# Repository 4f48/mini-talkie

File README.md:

# mini-talkie

A little 868 MHz walkie-talkie with LoRa radio for long ranges with built-in battery and USB-C charging.

### Features:
- 100% off-grid. Works anywhere!
- Long range: multiple kilometers in ideal conditions
- Long battery life: 1200 mAh lithium-polymer battery
- Convenient USB-C charging
- Swappable antenna: use any 868 MHz antenna you want
- Multiple modes: push-to-talk, voice activation
- Small size: fits in your pockets

### Usage:
1. Turn it on using the switch on the left.
2. Start talking! Use the push-to-talk button, or switch to voice activation and talk hands free.
3. Battery low? Plug it in to your regular phone charger.

## Why?
All the walkie-talkies I tried before have too short range, have too many fancy features I would never use, or are very expensive. This walkie-talkie is unique in the way that it uses LoRa radio, making it operate through exceptional ranges. It's also dead simple: no screen, no dials. It doesn't have many extra features, but the ones it has just work. It is also not very expensive to build. It's great for hiking so nobody gets lost, or multiple-car road trips to keep in contact with the other cars without phone calls.

## Assembly
You can actually build a mini-talkie for yourself. All you need is the PCB, SMD components, a speaker, an antenna and internal antenna cable. Below is a rough guide to making one.

### 1. PCB and components

The printed circuit board has to be manufactured somewhere. I recommend [Aisler](https://aisler.net) or [JLCPCB](https://jlcpcb.com), but any similar services work. You can find the source files for the PCB in [/pcb](./pcb). Make sure to order the PCBA (assembly) service if you are not comfortable soldering smaller sized components.

You also need some other components ordered. Check out the [Bill of Materials](./bom.csv) which includes links to help you order them easily.

| Component                          | MPN                | Reference                     | Qty | Link                                                                            |
|------------------------------------|--------------------|-------------------------------|-----|---------------------------------------------------------------------------------|
| 0603 2.2 µF capacitor              | CC0603KRX7R5BB225  | C1,C2                         | 2   | https://www.digikey.hu/short/4rjpq33n                                           |
| 0603 100 nF capacitor              | CC0603KRX7R5BB104  | C3,C4,C5,C6,C7,C9,C14,C18,C19 | 9   | https://www.digikey.hu/short/dt7hb4qj                                           |
| 0805 10 µF capacitor               | CL21A106KQFNNNG    | C8,C10,C11,C12,C13,C20        | 6   | https://www.digikey.hu/short/tvz058r0                                           |
| 0603 1 µF capacitor                | CL10A105KQ8NNNC    | C15,C16                       | 2   | https://www.digikey.hu/short/z9n48j83                                           |
| 0603 10 µF capacitor               | GRM188R60J106KE47D | C17                           | 1   | https://www.digikey.hu/short/4j9w29qw                                           |
| Schottky diode                     | B0520WS-7-F        | D1                            | 1   | https://www.digikey.hu/short/ht5bt73v                                           |
| 0805 orange LED                    | LTST-C170KFKT      | D2                            | 1   | https://www.digikey.hu/short/45p872b7                                           |
| 0603 ferrite bead 600 Ω @100 MHz   | BLM18KG601SN1D     | FB1                           | 1   | https://www.digikey.hu/short/0mqd98np                                           |
| SWD connector                      | BM03B-SRSS-TB      | J1                            | 1   | https://www.digikey.hu/short/5p581w55                                           |
| USB-C receptacle                   | USB4085-GF-A       | J2                            | 1   | https://www.digikey.hu/short/b77q7dpn                                           |
| battery connector                  | S2B-PH-K-S         | J3                            | 1   | https://www.digikey.hu/short/4j185jz8                                           |
| speaker connector                  | S2B-PH-K-S         | J4                            | 1   | https://www.digikey.hu/short/4j185jz8                                           |
| microphone                         | TOW-3050P-B-R      | MK1                           | 1   | https://www.digikey.hu/short/pvdf25rr                                           |
| MOSFET                             | AO3401A            | Q1                            | 1   | https://www.digikey.hu/short/8rwf7289                                           |
| 0603 10 kΩ resistor                | RC0603FR-0710KL    | R1,R4,R5,R6                   | 4   | https://www.digikey.hu/short/b31dpcpj                                           |
| 0603 5.1 kΩ resistor               | RC0603FR-075K1L    | R2,R3,R7                      | 3   | https://www.digikey.hu/short/q0d4nh3t                                           |
| 0805 1 kΩ resistor                 | ESR10EZPF1001      | R8                            | 1   | https://www.digikey.hu/short/5hnt9d3r                                           |
| SP3T sliding right-angle switch    | OS103011MA7QP1C    | SW1                           | 1   | https://www.digikey.hu/short/jz8f2558                                           |
| SPDT sliding right-angle switch    | OS102011MA1QN1     | SW2                           | 1   | https://www.digikey.hu/short/1v0t4jtn                                           |
| SPST right-angle pushbutton switch | B3F-3152           | SW3                           | 1   | https://www.digikey.hu/short/0rj93f0h                                           |
| microcontroller                    | STM32H503CBT6      | U1                            | 1   | https://www.digikey.hu/short/n7f3hf4p                                           |
| LoRa chipset                       | 114993390          | U2                            | 1   | https://www.digikey.hu/short/prpdvndd                                           |
| amplifier                          | PAM8302AASCR       | U3                            | 1   | https://www.digikey.hu/short/0pzv4hpb                                           |
| battery charger                    | MCP73831T-2ACI/OT  | U4                            | 1   | https://www.digikey.hu/short/wfqbhvzq                                           |
| 3.3V LDO voltage regulator         | RT9080-33GJ5       | U5                            | 1   | https://www.digikey.hu/short/2h9019td                                           |
| speaker                            | 4227               | -                             | 1   | https://www.digikey.hu/short/59fcjjq4                                           |
| antenna                            | GHX-325ASA3B       | -                             | 1   | https://www.digikey.hu/short/fqjjtd0b                                           |
| antenna cable                      | 18568              | -                             | 1   | https://www.digikey.hu/short/jn7jd79m                                           |
| battery                            | AKY0622            | -                             | 1   | https://www.tme.eu/hu/details/aky-lp883440/akkumulatorok/akyga-battery/aky0622/ |
| 2-pin JST PH cable                 | 4714               | -                             | 1   | https://www.digikey.hu/short/8mm8t1d7                                           |

Total cost of components: $38,82/unit (excl. taxes)

### 2. Printed parts

mini-talkie's enclosure is made from 2 parts. These have to be made on a 3D printer. If you don't have access to a 3D priner, explore services like [JLC3DP](https://jlc3dp.com) that print and ship the parts to you.

You can find the source files in [/3d](./3d) and exported models [/3d/exports](./3d/exports) for printing in STEP format.

### 3. Soldering

A fine-tipped soldering iron and some flux is needed for this part. Refer to the PCB source files in [/pcb](./pcb) as a reference for placing the correct parts.

Skip this step if you ordered your PCBs assembled (PCBA).

In addition, you need to remove the included connectors from the speaker and battery and solder on the 2-pin JST PH connectors you ordered instead. You need to do this even if you ordered a PCBA.

### 4. Programming

You need a Raspberry Pi Zero (2) or a separate debugger. Connect it to the SWD port on the circuit board and load the firmware from [/firmware](./firmware).

> TODO: Complete this part with instructions once the code is actually done.

### 5. Assembly
1. Insert 3 threaded inserts in the correct holes on the bottom enclosure. Appropriate tools are needed for this step.
2. Install the antenna cable using the included washers and nut.
3. Peel the protective layer off the adhesive on the speaker and stick it on the top enclosure, behind the speaker grille, but in a way that it won't obstruct the microphone.
4. Drop the battery into the compartment under where the PCB goes and plug it into the board.
5. Place the board on the bottom enclosure so that the battery connector is facing down.
6. Plug in the speaker to the board, and put the top enclosure on the bottom, then screw all the M2.5 screws into the top enclosure. Those 3 screws hold everything together, so make sure they are secure.
7. Compete the build by installing your SMA antenna on the top.

## Fallout Zine

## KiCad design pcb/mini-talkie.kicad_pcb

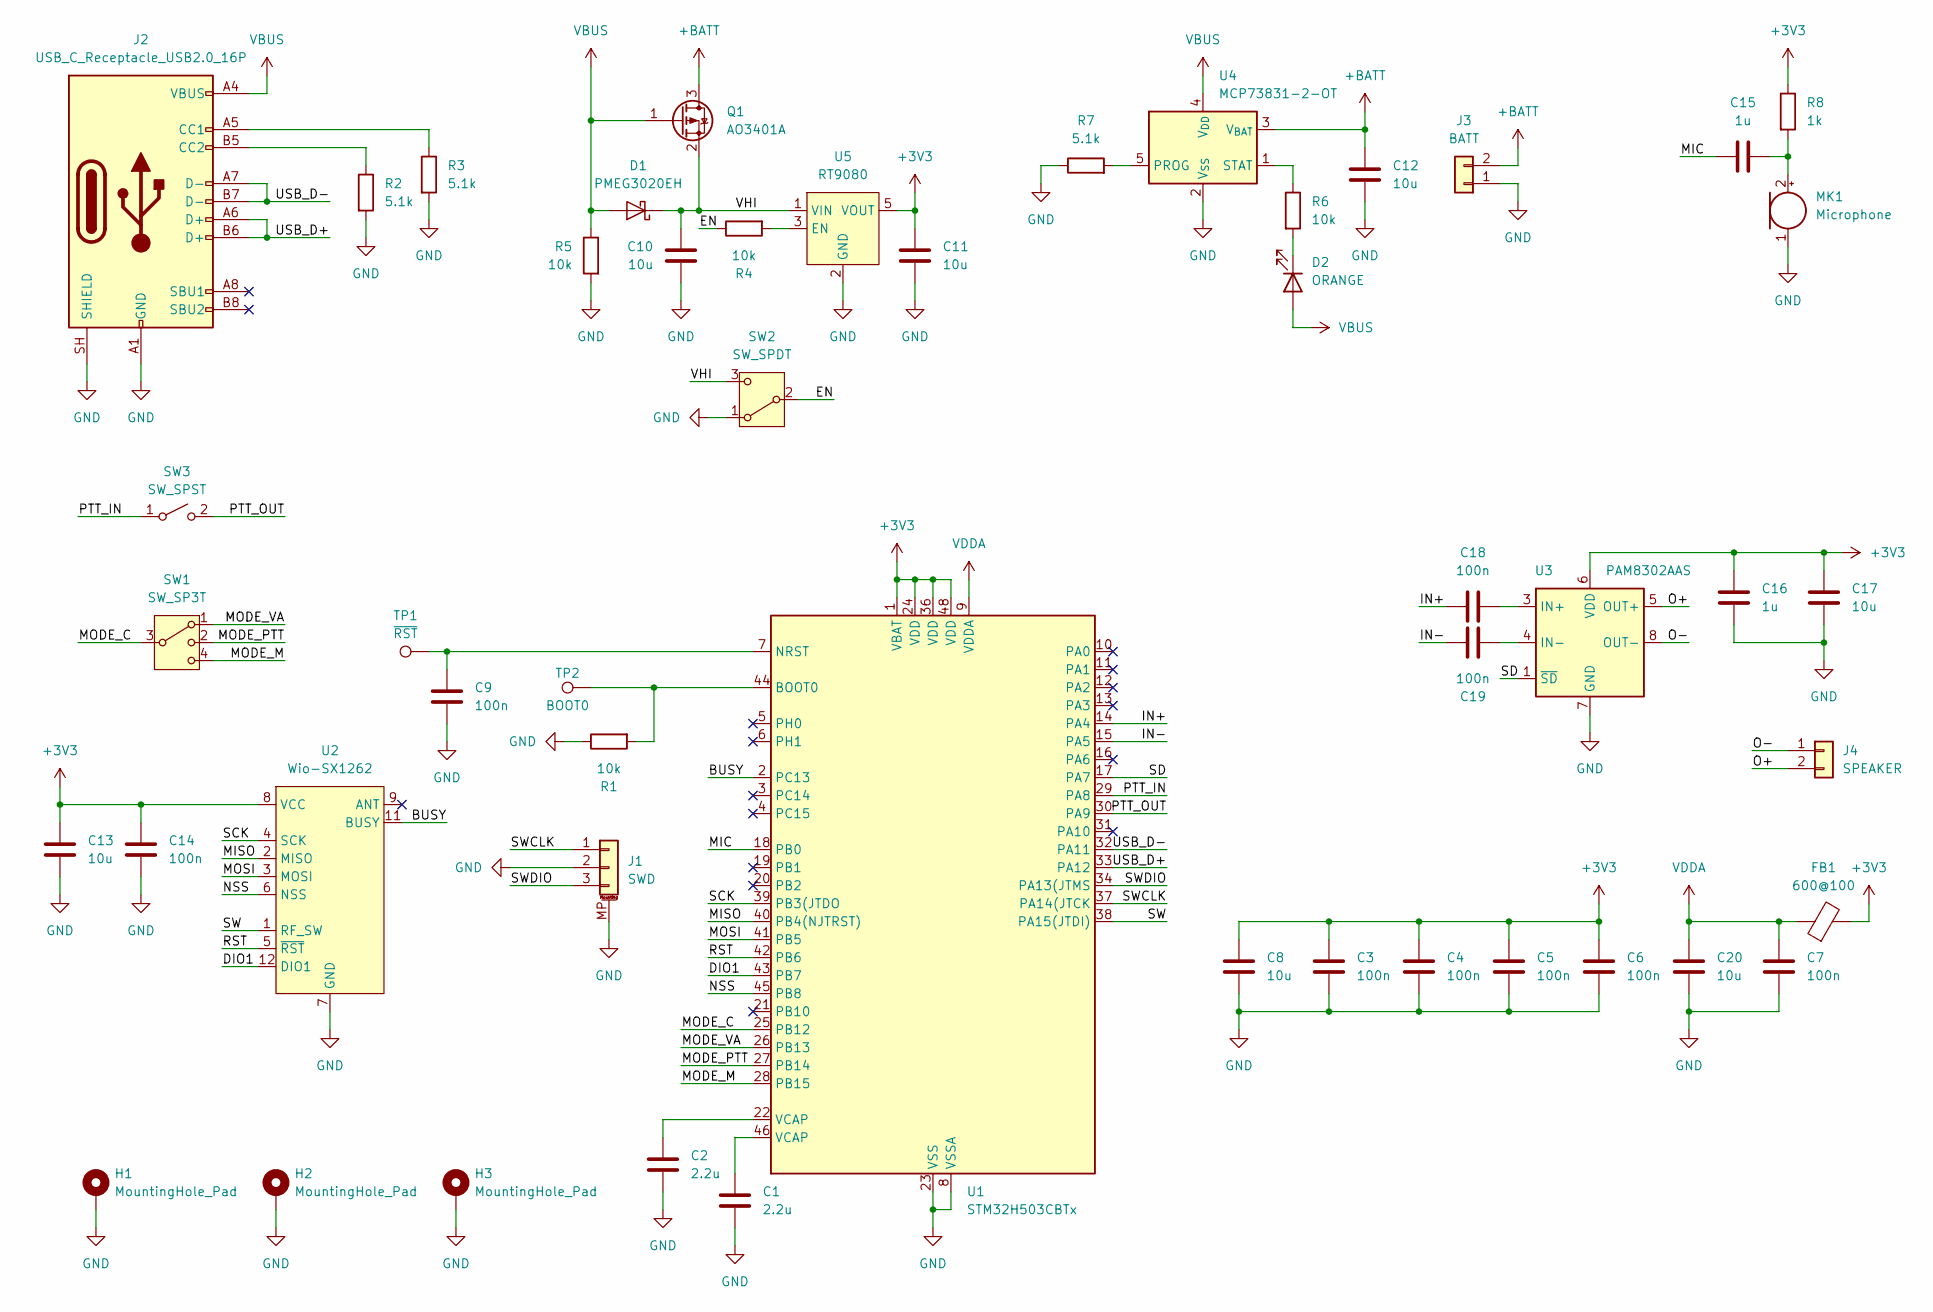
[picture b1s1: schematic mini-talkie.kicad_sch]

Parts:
C1, C2: 2.2u; C_0603_1608Metric_Pad1.08x0.95mm_HandSolder
C3, C4, C5, C6, C7, C9, C14, C18, C19: 100n; C_0603_1608Metric_Pad1.08x0.95mm_HandSolder
C8, C10, C11, C12, C13, C20: 10u; C_0805_2012Metric_Pad1.18x1.45mm_HandSolder
C15, C16: 1u; C_0603_1608Metric_Pad1.08x0.95mm_HandSolder
C17: 10u; C_0603_1608Metric_Pad1.08x0.95mm_HandSolder
D1: PMEG3020EH; D_SMA_Handsoldering
D2: ORANGE; LED_0805_2012Metric_Pad1.15x1.40mm_HandSolder
FB1: 600@100; L_0603_1608Metric_Pad1.05x0.95mm_HandSolder; MPN BLM18KG601SN1D
H1, H2, H3: MountingHole_Pad; MountingHole_2.7mm_M2.5_ISO7380_Pad
J1: SWD; JST_SH_BM03B-SRSS-TB_1x03-1MP_P1.00mm_Vertical
J2: USB_C_Receptacle_USB2.0_16P; USB_C_Receptacle_GCT_USB4085
J3: BATT; JST_PH_S2B-PH-K_1x02_P2.00mm_Horizontal
J4: SPEAKER; JST_PH_S2B-PH-K_1x02_P2.00mm_Horizontal
MK1: Microphone; PUI_THT-2; MPN TOW-3050P-B-R
Q1: AO3401A; SOT-23
R1, R4, R5, R6: 10k; R_0603_1608Metric_Pad0.98x0.95mm_HandSolder
R2, R3, R7: 5.1k; R_0603_1608Metric_Pad0.98x0.95mm_HandSolder
R8: 1k; R_0805_2012Metric_Pad1.20x1.40mm_HandSolder
SW1: SW_SP3T; CK_SW_SP3T_OS103011MA7QP1C; MPN OS103011MA7QP1C
SW2: SW_SPDT; SW_Slide_SPDT_Angled_CK_OS102011MA1Q; MPN OS102011MA1QN1
SW3: SW_SPST; SW_SPST_Omron_B3F-315x_Angled; MPN B3F-3152
TP1: ~{RST}; TestPoint_Pad_D2.0mm
TP2: BOOT0; TestPoint_Pad_D2.0mm
U1: STM32H503CBTx; LQFP-48_7x7mm_P0.5mm; MPN STM32H503CBT6
U2: Wio-SX1262; Seeed_SMD-12; MPN 114993390
U3: PAM8302AAS; MSOP-8_3x3mm_P0.65mm; MPN PAM8302AASCR
U4: MCP73831-2-OT; SOT-23-5; MPN MCP73831T-2ACI/OT
U5: RT9080; TSOT-23-5; MPN RT9080-33GJ5

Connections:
+3V3: C3.1, C4.1, C5.1, C6.1, C8.1, C11.1, C13.1, C14.1, C16.1, C17.1, FB1.2, R8.1, U1.1 (VBAT), U1.24 (VDD), U1.36 (VDD), U1.48 (VDD), U2.8 (VCC), U3.6 (VDD), U5.5 (VOUT)
+BATT: C12.1, J3.2, Q1.3 (D), U4.3 (V_{BAT})
/BUSY: U1.2 (PC13), U2.11 (BUSY)
/DIO1: U1.43 (PB7), U2.12 (DIO1)
/EN: R4.1, SW2.2 (B)
/IN+: C18.1, U1.14 (PA4)
/IN-: C19.1, U1.15 (PA5)
/MIC: C15.1, U1.18 (PB0)
/MISO: U1.40 (PB4(NJTRST)), U2.2 (MISO)
/MODE_C: SW1.3, U1.25 (PB12)
/MODE_M: SW1.4, U1.28 (PB15)
/MODE_PTT: SW1.2, U1.27 (PB14)
/MODE_VA: SW1.1, U1.26 (PB13)
/MOSI: U1.41 (PB5), U2.3 (MOSI)
/NSS: U1.45 (PB8), U2.6 (NSS)
/O+: J4.2, U3.5 (OUT+)
/O-: J4.1, U3.8 (OUT-)
/PTT_IN: SW3.1 (A), U1.29 (PA8)
/PTT_OUT: SW3.2 (B), U1.30 (PA9)
/RST: U1.42 (PB6), U2.5 (~RST)
/SCK: U1.39 (PB3(JTDO), U2.4 (SCK)
/SD: U1.17 (PA7), U3.1 (~SD)
/SW: U1.38 (PA15(JTDI)), U2.1 (RF_SW)
/SWCLK: J1.1, U1.37 (PA14(JTCK)
/SWDIO: J1.3, U1.34 (PA13(JTMS)
/USB_D+: J2.A6 (D+), J2.B6 (D+), U1.33 (PA12)
/USB_D-: J2.A7 (D-), J2.B7 (D-), U1.32 (PA11)
/VHI: C10.1, D1.1 (K), Q1.2 (S), SW2.3 (C), U5.1 (VIN)
GND: C1.1, C2.1, C3.2, C4.2, C5.2, C6.2, C7.2, C8.2, C9.2, C10.2, C11.2, C12.2, C13.2, C14.2, C16.2, C17.2, C20.2, H1.1 (1_1), H2.1 (1_1), H3.1 (1_1), J1.2, J1.MP (MountPin), J2.A1 (GND), J2.A12 (GND), J2.B1 (GND), J2.B12 (GND), J2.SH (SHIELD), J3.1, MK1.1 (-), R1.1, R2.2, R3.2, R5.2, R7.1, SW2.1 (A), U1.8 (VSSA), U1.23 (VSS), U1.35 (VSS), U1.47 (VSS), U2.7 (GND), U2.10 (GND), U3.7 (GND), U4.2 (V_{SS}), U5.2 (GND), U5.4 (GND)
unnamed: C1.2, U1.46 (VCAP)
unnamed: C2.2, U1.22 (VCAP)
unnamed: D2.1 (K), R6.2
unnamed: J2.A5 (CC1), R3.1
unnamed: J2.B5 (CC2), R2.1
unnamed: C15.2, MK1.2 (+), R8.2
unnamed: R1.2, TP2.1 (1_1), U1.44 (BOOT0)
unnamed: C9.1, TP1.1 (1_1), U1.7 (NRST)
unnamed: C18.2, U3.3 (IN+)
unnamed: C19.2, U3.4 (IN-)
unnamed: R7.2, U4.5 (PROG)
unnamed: R6.1, U4.1 (STAT)
unnamed: R4.2, U5.3 (EN)
VBUS: D1.2 (A), D2.2 (A), J2.A4 (VBUS), J2.A9 (VBUS), J2.B4 (VBUS), J2.B9 (VBUS), Q1.1 (G), R5.1, U4.4 (V_{DD})
VDDA: C7.1, C20.1, FB1.1, U1.9 (VDDA)

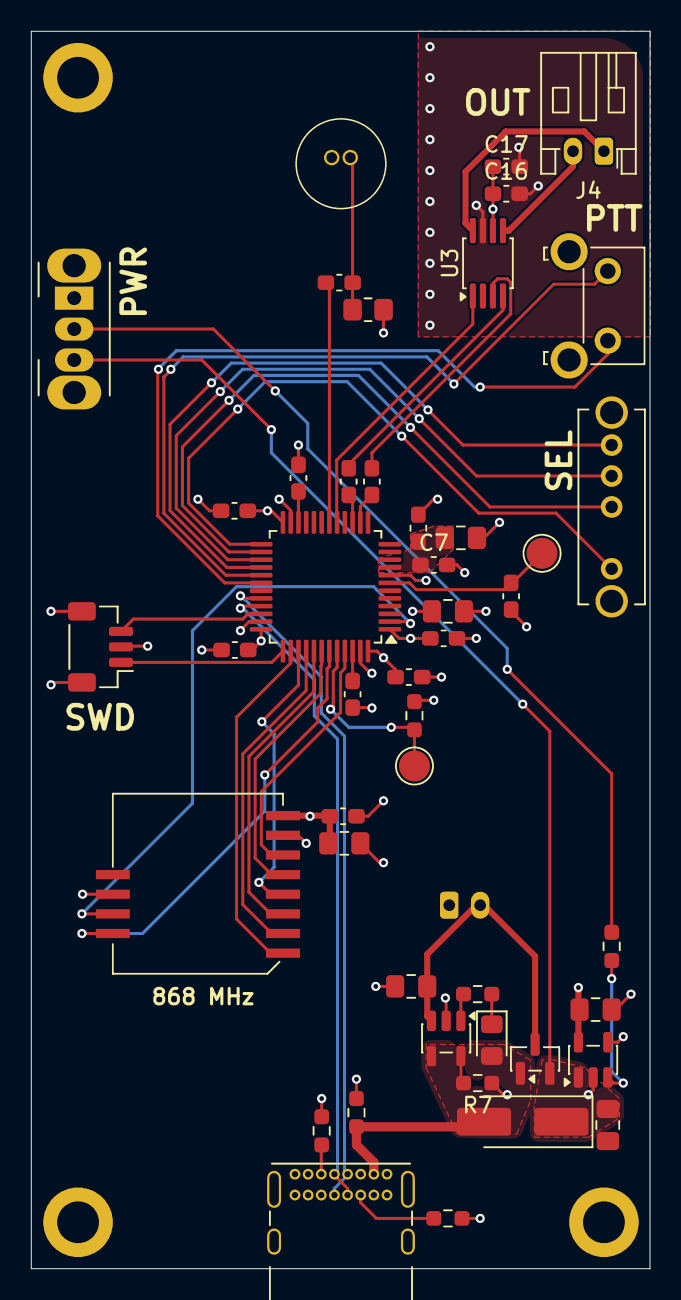
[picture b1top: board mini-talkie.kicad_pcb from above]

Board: 4 copper layers, 40.0 x 80.0 mm, 50 parts (1 on the bottom side), 44 nets.

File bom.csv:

"Reference","Qty","Value","DNP","Exclude from BOM","Exclude from Board","Footprint","Datasheet","MPN"
"C1,C2","2","2.2u","","","","Capacitor_SMD:C_0603_1608Metric_Pad1.08x0.95mm_HandSolder","",""
"C3,C4,C5,C6,C7,C9,C14,C18,C19","9","100n","","","","Capacitor_SMD:C_0603_1608Metric_Pad1.08x0.95mm_HandSolder","",""
"C8,C10,C11,C12,C13,C20","6","10u","","","","Capacitor_SMD:C_0805_2012Metric_Pad1.18x1.45mm_HandSolder","",""
"C15,C16","2","1u","","","","Capacitor_SMD:C_0603_1608Metric_Pad1.08x0.95mm_HandSolder","",""
"C17","1","10u","","","","Capacitor_SMD:C_0603_1608Metric_Pad1.08x0.95mm_HandSolder","",""
"D1","1","PMEG3020EH","","","","Diode_SMD:D_SMA_Handsoldering","https://assets.nexperia.com/documents/data-sheet/PMEG3020EH_EJ.pdf",""
"D2","1","ORANGE","","","","LED_SMD:LED_0805_2012Metric_Pad1.15x1.40mm_HandSolder","",""
"FB1","1","600@100","","","","Inductor_SMD:L_0603_1608Metric_Pad1.05x0.95mm_HandSolder","","BLM18KG601SN1D"
"J1","1","SWD","","","","Connector_JST:JST_SH_BM03B-SRSS-TB_1x03-1MP_P1.00mm_Vertical","",""
"J2","1","USB_C_Receptacle_USB2.0_16P","","","","Connector_USB:USB_C_Receptacle_GCT_USB4085","https://www.usb.org/sites/default/files/documents/usb_type-c.zip",""
"J3","1","BATT","","","","Connector_JST:JST_PH_S2B-PH-K_1x02_P2.00mm_Horizontal","",""
"J4","1","SPEAKER","","","","Connector_JST:JST_PH_S2B-PH-K_1x02_P2.00mm_Horizontal","",""
"MK1","1","Microphone","","","","Mini_Talkie:PUI_THT-2","https://mm.digikey.com/Volume0/opasdata/d220001/medias/docus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","TOW-3050P-B-R "
"Q1","1","AO3401A","","","","Package_TO_SOT_SMD:SOT-23","http://www.aosmd.com/pdfs/datasheet/AO3401A.pdf",""
"R1,R4,R5,R6","4","10k","","","","Resistor_SMD:R_0603_1608Metric_Pad0.98x0.95mm_HandSolder","",""
"R2,R3,R7","3","5.1k","","","","Resistor_SMD:R_0603_1608Metric_Pad0.98x0.95mm_HandSolder","",""
"R8","1","1k","","","","Resistor_SMD:R_0805_2012Metric_Pad1.20x1.40mm_HandSolder","",""
"SW1","1","SW_SP3T","","","","Mini_Talkie:CK_SW_SP3T_OS103011MA7QP1C","","OS103011MA7QP1C"
"SW2","1","SW_SPDT","","","","Button_Switch_THT:SW_Slide_SPDT_Angled_CK_OS102011MA1Q","","OS102011MA1QN1"
"SW3","1","SW_SPST","","","","Button_Switch_THT:SW_SPST_Omron_B3F-315x_Angled","","B3F-3152"
"U1","1","STM32H503CBTx","","","","Package_QFP:LQFP-48_7x7mm_P0.5mm","https://www.st.com/resource/en/datasheet/stm32h503cb.pdf","STM32H503CBT6"
"U2","1","Wio-SX1262","","","","Mini_Talkie:Seeed_SMD-12","https://files.seeedstudio.com/products/SenseCAP/Wio_SX1262/W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","114993390"
"U3","1","PAM8302AAS","","","","Package_SO:MSOP-8_3x3mm_P0.65mm","https://www.diodes.com/assets/Datasheets/PAM8302A.pdf","PAM8302AASCR"
"U4","1","MCP73831-2-OT","","","","Package_TO_SOT_SMD:SOT-23-5","http://ww1.microchip.com/downloads/en/DeviceDoc/20001984g.pdf","MCP73831T-2ACI/OT"
"U5","1","RT9080","","","","Package_TO_SOT_SMD:TSOT-23-5","https://www.richtek.com/SaveDownload.aspx?specid=RT9080","RT9080-33GJ5"

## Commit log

2026-05-23 mcu, radio, mic footprints
2026-05-24 switches, power supply
2026-05-25 schematic almost done
2026-05-26 get started with layout
2026-05-27 pcb routing
2026-05-28 silkscreen, 3d models
2026-05-28 start bom
2026-05-30 start enclosure
2026-05-31 cutouts, speaker grille
2026-06-01 continue 3d model
2026-06-02 docs, images
2026-06-02 fix links
2026-06-02 fix links 2
2026-06-02 fix links 3
2026-06-02 fix links 4
2026-06-02 start compiling complete bom
2026-06-02 remove lockfile
2026-06-03 continue bom
2026-06-06 add bom preview and estimated cost
2026-06-06 add zine
2026-06-06 cleanup
2026-06-06 add exports

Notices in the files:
pcb/mini-talkie.kicad_pcb:
Copyright © 2026
